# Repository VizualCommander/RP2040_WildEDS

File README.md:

# RP2040_WildEDS
IoT environmental sensor used to predict wildfires

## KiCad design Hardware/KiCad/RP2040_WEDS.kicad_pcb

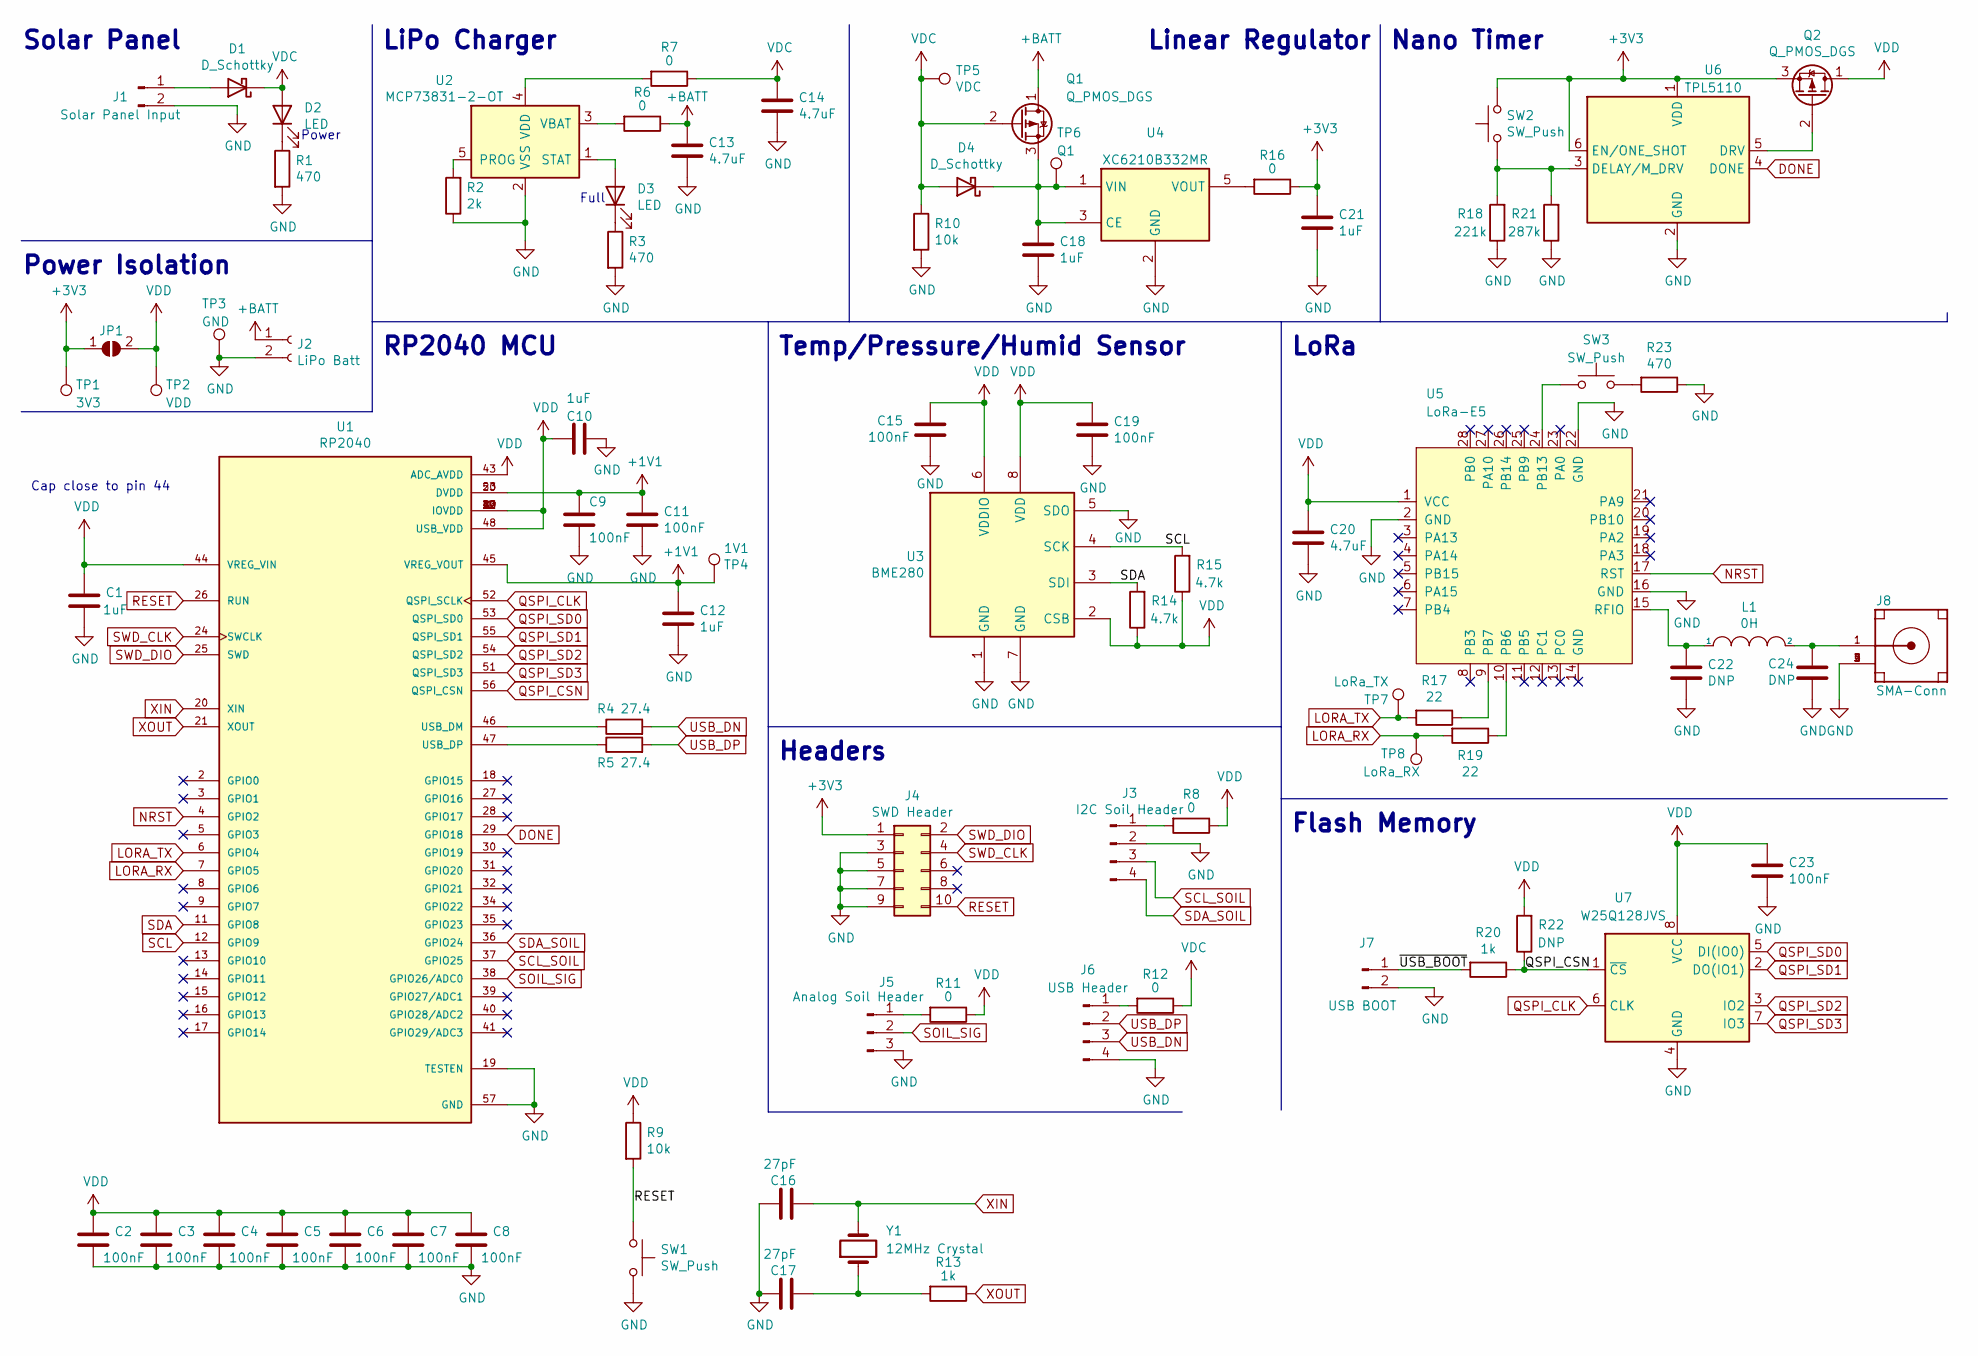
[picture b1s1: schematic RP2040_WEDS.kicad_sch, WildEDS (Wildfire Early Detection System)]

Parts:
C1, C10, C12, C18, C21: 1uF; C_0603_1608Metric
C2, C3, C4, C5, C6, C7, C8, C9, C11, C15, C19, C23: 100nF; C_0603_1608Metric
C13, C14, C20: 4.7uF; C_0603_1608Metric
C16, C17: 27pF; C_0603_1608Metric
C22, C24: DNP; C_0603_1608Metric
D1, D4: D_Schottky; D_SOD-323
D2, D3: LED; LED_0603_1608Metric
J1: Solar Panel Input; PinHeader_1x02_P2.54mm_Horizontal
J2: LiPo Batt; PinHeader_2x01_P2.54mm_Vertical
J3: I2C Soil Header; PinHeader_1x04_P2.54mm_Horizontal
J4: SWD Header; PinHeader_2x05_P1.27mm_Vertical
J5: Analog Soil Header; PinHeader_1x03_P2.54mm_Horizontal
J6: USB Header; PinHeader_1x04_P2.54mm_Vertical
J7: USB BOOT; PinSocket_1x02_P2.54mm_Vertical
J8: SMA-Conn; SMA_Amphenol_132289_EdgeMount_new; PARTREV K
JP1: Power Isolation; SolderJumper-2_P1.3mm_Open_RoundedPad1.0x1.5mm
L1: 0H; L_0603_1608Metric
Q1, Q2: Q_PMOS_DGS; SOT-23
R1, R3, R23: 470; R_0603_1608Metric
R2: 2k; R_0603_1608Metric
R4, R5: 27.4; R_0603_1608Metric
R6, R7, R8, R11, R12, R16: 0; R_0603_1608Metric
R9, R10: 10k; R_0603_1608Metric
R13, R20: 1k; R_0603_1608Metric
R14, R15: 4.7k; R_0603_1608Metric
R17, R19: 22; R_0603_1608Metric
R18: 221k; R_0603_1608Metric
R21: 287k; R_0603_1608Metric
R22: DNP; R_0603_1608Metric
SW1, SW2, SW3: SW_Push; SW_Push_1P1T_NO_6x6mm_H9.5mm
TP1: 3V3; TestPoint_Loop_D1.80mm_Drill1.0mm_Beaded
TP2: VDD; TestPoint_Loop_D1.80mm_Drill1.0mm_Beaded
TP3: GND; TestPoint_Loop_D1.80mm_Drill1.0mm_Beaded
TP4: 1V1; TestPoint_Loop_D1.80mm_Drill1.0mm_Beaded
TP5: VDC; TestPoint_Loop_D1.80mm_Drill1.0mm_Beaded
TP6: Q1; TestPoint_Loop_D1.80mm_Drill1.0mm_Beaded
TP7: LoRa_TX; TestPoint_Loop_D1.80mm_Drill1.0mm_Beaded
TP8: LoRa_RX; TestPoint_Loop_D1.80mm_Drill1.0mm_Beaded
U1: RP2040; QFN40P700X700X90-57N; PARTREV 1.6.1
U2: MCP73831-2-OT; SOT-23-5
U3: BME280; Bosch_LGA-8_2.5x2.5mm_P0.65mm_ClockwisePinNumbering
U4: XC6210B332MR; SOT-23-5
U5: LoRa-E5
U6: TPL5110; SOT-23-6
U7: W25Q128JVS; SOIC-8_5.23x5.23mm_P1.27mm
Y1: 12MHz Crystal; XTAL1140X470X420N

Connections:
+1V1: C9.1, C11.1, C12.1, TP4.1, U1.23 (DVDD), U1.45 (VREG_VOUT), U1.50 (DVDD)
+3V3: C21.1, J4.1, JP1.1 (A), Q2.3 (S), R16.1, SW2.2, TP1.1, U6.1 (VDD), U6.6 (EN/ONE_SHOT)
+BATT: C13.1, J2.1, Q1.1 (D), R6.1
/~USB_BOOT: J7.1, R20.2
DONE: U1.29 (GPIO18), U6.4 (DONE)
GND: C1.2, C2.2, C3.2, C4.2, C5.2, C6.2, C7.2, C8.2, C9.2, C10.1, C11.2, C12.2, C13.2, C14.2, C15.2, C16.1, C17.1, C18.2, C19.2, C20.2, C21.2, C22.2, C23.2, C24.2, J1.2, J2.2, J3.2, J4.3, J4.5, J4.7, J4.9, J5.3, J6.4, J7.2, J8.2, J8.3, J8.4, J8.5, R1.2, R2.1, R3.2, R10.2, R18.1, R21.1, R23.1, SW1.2, TP3.1, U1.19 (TESTEN), U1.57 (GND), U2.2 (VSS), U3.1 (GND), U3.5 (SDO), U3.7 (GND), U4.2 (GND), U5.2 (GND), U5.16 (GND), U5.22 (GND), U6.2 (GND), U7.4 (GND)
LORA_RX: R19.2, TP8.1, U1.7 (GPIO5)
LORA_TX: R17.2, TP7.1, U1.6 (GPIO4)
NRST: U1.4 (GPIO2), U5.17 (RST)
unnamed: C17.2, R13.2, Y1.1
unnamed: C18.1, D4.1 (K), Q1.3 (S), TP6.1, U4.1 (VIN), U4.3 (CE)
unnamed: C22.1, L1.1, U5.15 (RFIO)
unnamed: C24.1, J8.1, L1.2
unnamed: D1.2 (A), J1.1
unnamed: D2.1 (K), R1.1
unnamed: D3.1 (K), R3.1
unnamed: D3.2 (A), U2.1 (STAT)
unnamed: J3.1, R8.2
unnamed: J5.1, R11.2
unnamed: J6.1, R12.2
unnamed: Q2.2 (G), U6.5 (DRV)
unnamed: R2.2, U2.5 (PROG)
unnamed: R4.1, U1.46 (USB_DM)
unnamed: R5.1, U1.47 (USB_DP)
unnamed: R6.2, U2.3 (VBAT)
unnamed: R7.2, U2.4 (VDD)
unnamed: R16.2, U4.5 (VOUT)
unnamed: R17.1, U5.9 (PB7)
unnamed: R18.2, R21.2, SW2.1, U6.3 (DELAY/M_DRV)
unnamed: R19.1, U5.10 (PB6)
unnamed: R23.2, SW3.2
unnamed: SW3.1, U5.24 (PB13~)
QSPI_CLK: U1.52 (QSPI_SCLK), U7.6 (CLK)
QSPI_CSN: R20.1, R22.1, U1.56 (QSPI_CSN), U7.1 (~CS)
QSPI_SD0: U1.53 (QSPI_SD0), U7.5 (DI(IO0))
QSPI_SD1: U1.55 (QSPI_SD1), U7.2 (DO(IO1))
QSPI_SD2: U1.54 (QSPI_SD2), U7.3 (IO2)
QSPI_SD3: U1.51 (QSPI_SD3), U7.7 (IO3)
RESET: J4.10, R9.2, SW1.1, U1.26 (RUN)
SCL: R15.2, U1.12 (GPIO9), U3.4 (SCK)
SCL_SOIL: J3.3, U1.37 (GPIO25)
SDA: R14.2, U1.11 (GPIO8), U3.3 (SDI)
SDA_SOIL: J3.4, U1.36 (GPIO24)
SOIL_SIG: J5.2, U1.38 (GPIO26/ADC0)
SWD_CLK: J4.4, U1.24 (SWCLK)
SWD_DIO: J4.2, U1.25 (SWD)
USB_DN: J6.3, R4.2
USB_DP: J6.2, R5.2
VDC: C14.1, D1.1 (K), D2.2 (A), D4.2 (A), Q1.2 (G), R7.1, R10.1, R12.1, TP5.1
VDD: C1.1, C2.1, C3.1, C4.1, C5.1, C6.1, C7.1, C8.1, C10.2, C15.1, C19.1, C20.1, C23.1, JP1.2 (B), Q2.1 (D), R8.1, R9.1, R11.1, R14.1, R15.1, R22.2, TP2.1, U1.1 (IOVDD), U1.10 (IOVDD), U1.22 (IOVDD), U1.33 (IOVDD), U1.42 (IOVDD), U1.43 (ADC_AVDD), U1.44 (VREG_VIN), U1.48 (USB_VDD), U1.49 (IOVDD), U3.2 (CSB), U3.6 (VDDIO), U3.8 (VDD), U5.1 (VCC), U7.8 (VCC)
XIN: C16.2, U1.20 (XIN), Y1.2
XOUT: R13.1, U1.21 (XOUT)

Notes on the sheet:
LiPo Charger
Linear Regulator
Solar Panel
RP2040 MCU
Full
Headers
Power Isolation
Nano Timer
LoRa
Temp/Pressure/Humid Sensor
Power
Flash Memory
Cap close to pin 44

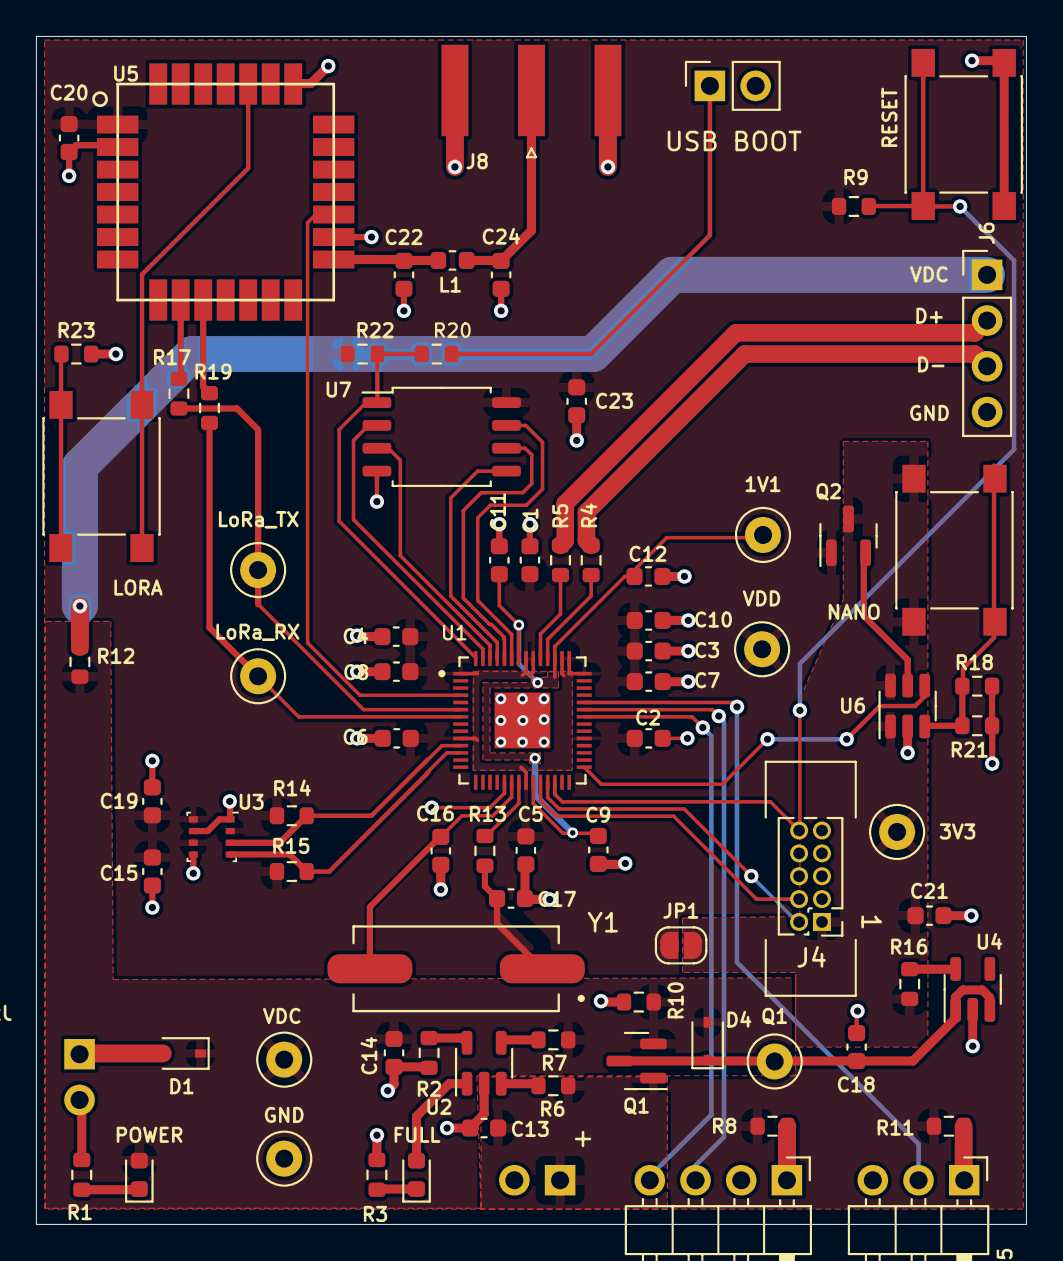
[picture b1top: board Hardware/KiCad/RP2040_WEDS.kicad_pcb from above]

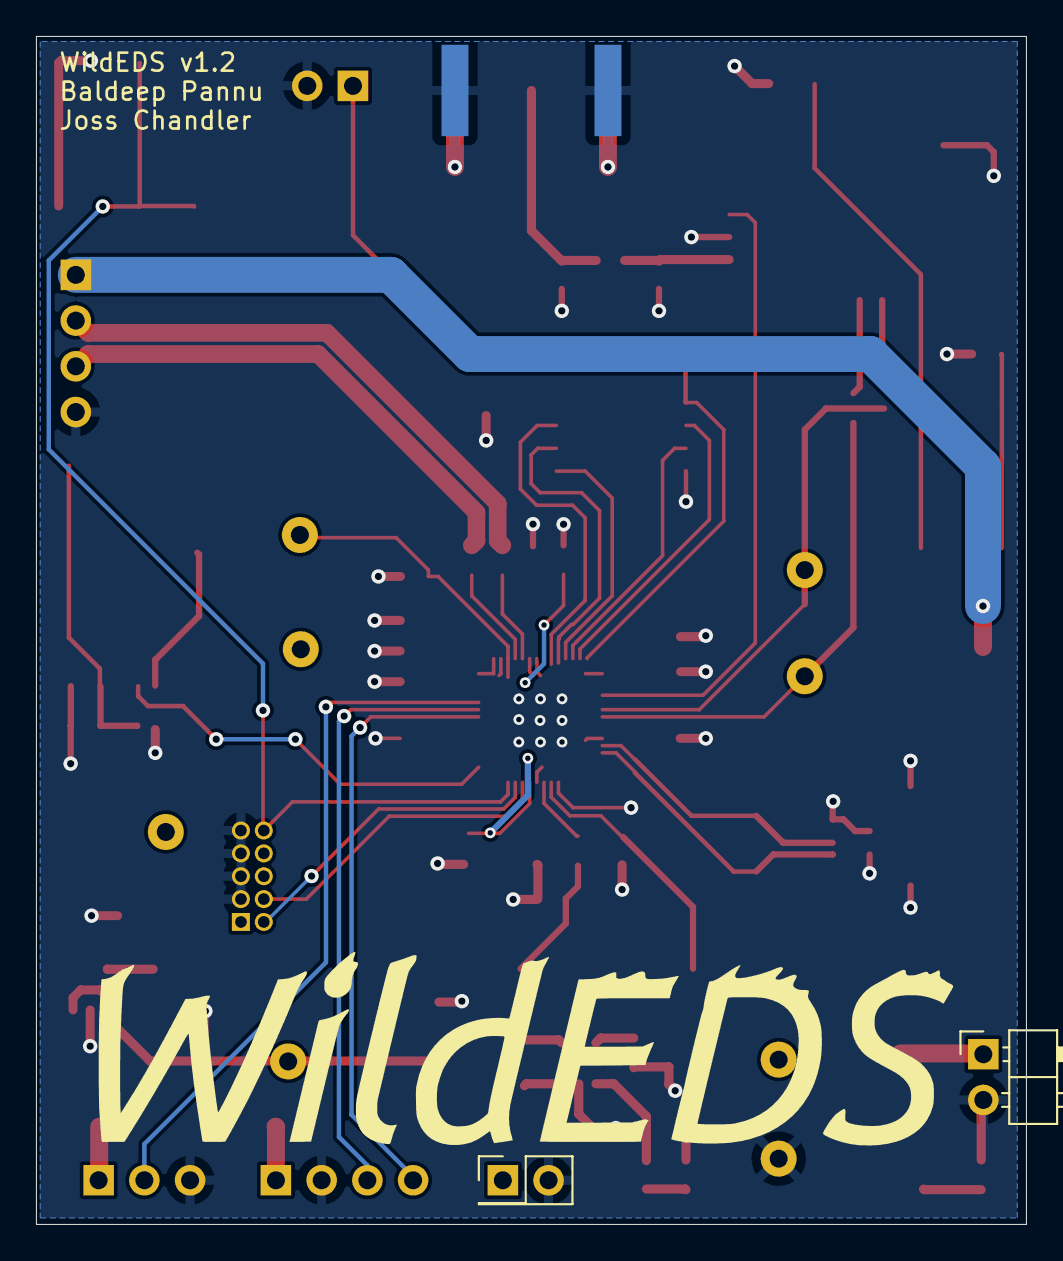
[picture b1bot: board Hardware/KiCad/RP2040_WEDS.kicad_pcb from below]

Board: 2 copper layers, 55.0 x 66.0 mm, 82 parts (2 on the bottom side), 52 nets.

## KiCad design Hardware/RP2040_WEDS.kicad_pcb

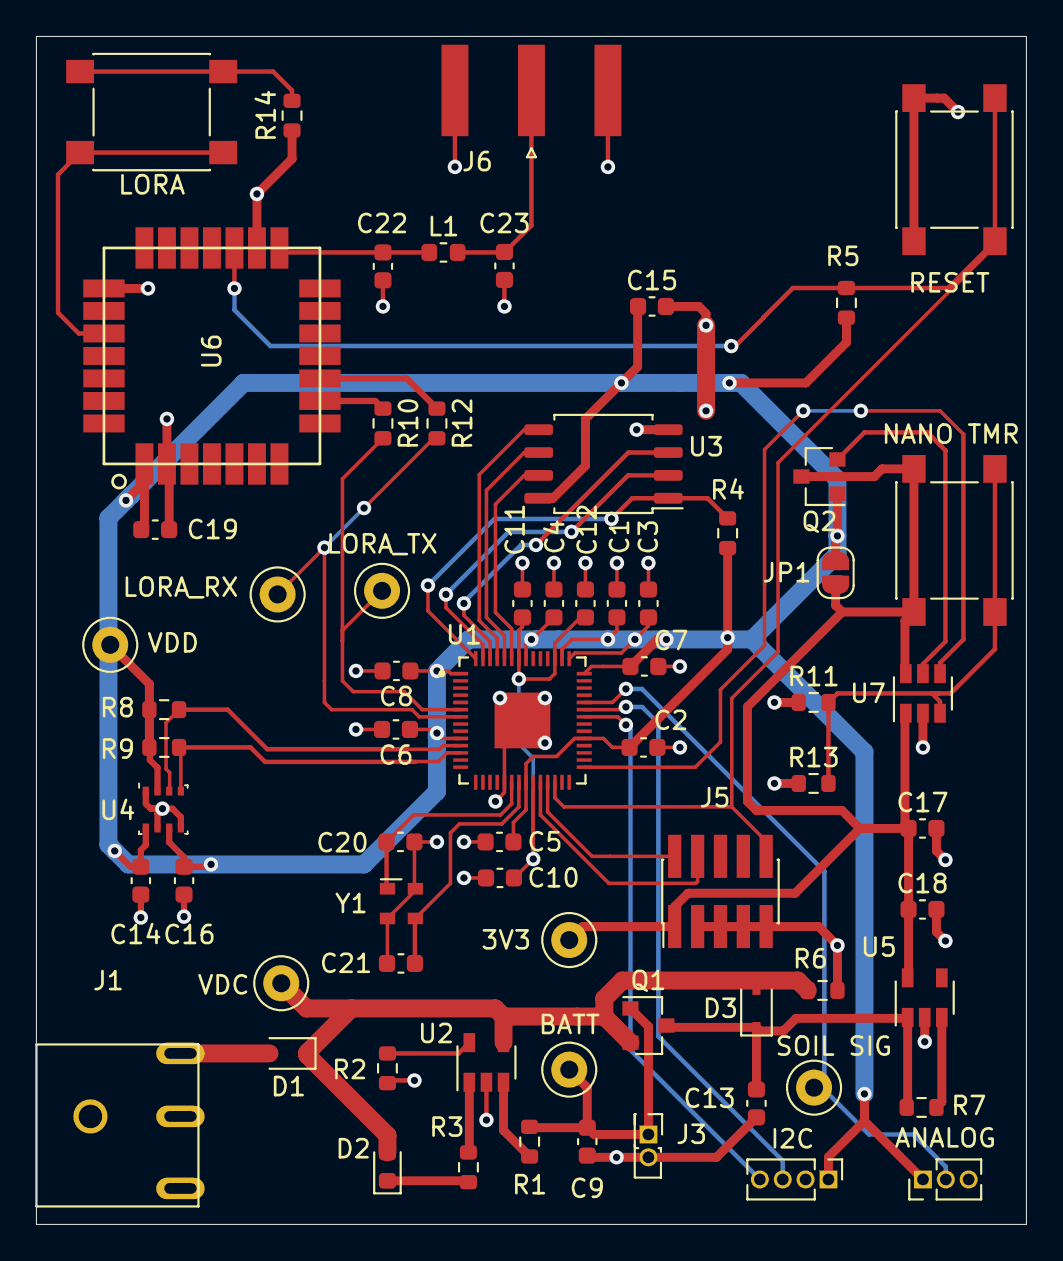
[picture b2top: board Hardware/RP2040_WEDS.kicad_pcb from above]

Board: 2 copper layers, 55.0 x 66.0 mm, 68 parts (0 on the bottom side), 40 nets.

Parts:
3V3: TestPoint; TestPoint_Loop_D1.80mm_Drill1.0mm_Beaded
ANALOG: Conn_01x03_Male; PinHeader_1x03_P1.27mm_Vertical
BATT: TestPoint; TestPoint_Loop_D1.80mm_Drill1.0mm_Beaded
C1, C12: 1uF; C_0603_1608Metric
C2, C3, C4, C5, C6, C7, C8, C10, C11, C14, C16: 100nF; C_0603_1608Metric
C9, C13, C17, C18: 10uF; C_0603_1608Metric
C15: C; C_0603_1608Metric
C19: 4.7uF; C_0603_1608Metric
C20, C21: 8pF; C_0603_1608Metric
C22, C23: DNP; C_0603_1608Metric
D1, D3: D_Schottky; D_SOD-323
D2: LED; LED_0603_1608Metric
I2C: Conn_01x04_Male; PinHeader_1x04_P1.27mm_Vertical
J1: Barrel_Jack_Switch_Pin3Ring; 54-00125
J3: LiPo Batt; PinHeader_2x01_P1.27mm_Vertical
J5: Conn_02x05_Odd_Even; PinHeader_2x05_P1.27mm_Vertical_SMD
J6: SMA-J-P-H-RA-TH1; SMA_Amphenol_132289_EdgeMount_new
JP1: SolderJumper_2_Open; SolderJumper-2_P1.3mm_Open_RoundedPad1.0x1.5mm
L1: 0H; L_0603_1608Metric
LORA: SW_Push; SW_Push_1P1T_NO_6x6mm_H9.5mm
LORA_RX: TestPoint; TestPoint_Loop_D1.80mm_Drill1.0mm_Beaded
LORA_TX: TestPoint; TestPoint_Loop_D1.80mm_Drill1.0mm_Beaded
NANO TMR: SW_Push; SW_Push_1P1T_NO_6x6mm_H9.5mm
Q1, Q2: Q_PMOS_DGS; SOT-23
R1: 0; R_0603_1608Metric
R2: 2k; R_0603_1608Metric
R3, R4, R5, R6, R7, R8, R9: 10k; R_0603_1608Metric
R10, R12: 22; R_0603_1608Metric
R11: 221k; R_0603_1608Metric
R13: 287k; R_0603_1608Metric
R14: 470; R_0603_1608Metric
RESET: SW_Push; SW_Push_1P1T_NO_6x6mm_H9.5mm
SOIL SIG: TestPoint; TestPoint_Loop_D1.80mm_Drill1.0mm_Beaded
U1: RP2040; QFN40P700X700X90-57N
U2: MCP73831-2-OT; SOT-23-5
U3: W25Q128JVS; SOIC-8_5.23x5.23mm_P1.27mm
U4: BME280; Bosch_LGA-8_2.5x2.5mm_P0.65mm_ClockwisePinNumbering
U5: AP2112K-3.3; SOT-23-5
U6: LoRa-E5
U7: TPL5110; SOT-23-6
VDC: TestPoint; TestPoint_Loop_D1.80mm_Drill1.0mm_Beaded
VDD: TestPoint; TestPoint_Loop_D1.80mm_Drill1.0mm_Beaded
Y1: Crystal_GND24; Oscillator_SMD_Abracon_ASDMB-4Pin_2.5x2.0mm

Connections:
+1V1: C10.1, C11.1, C12.1, U1.23, U1.45, U1.50
+3V3: 3V3.1, C17.1, C18.1, J5.1, JP1.1, NANO TMR.2, Q2.3, U5.5, U7.1, U7.6
+BATT: BATT.1, C9.1, J3.1, Q1.1, R1.1
DONE: U1.29, U7.4
GND: ANALOG.3, C1.2, C2.2, C3.2, C4.2, C5.2, C6.2, C7.2, C8.2, C9.2, C10.2, C11.2, C12.2, C13.2, C14.2, C15.2, C16.2, C17.2, C18.2, C19.2, C20.2, C21.1, C22.2, C23.2, I2C.2, J1.2, J1.3, J3.2, J5.3, J5.5, J5.7, J5.9, J6.2, J6.3, J6.4, J6.5, R2.1, R6.2, R11.1, R13.1, R14.1, RESET.2, U1.19, U1.57, U2.2, U3.4, U4.1, U4.5, U4.7, U5.2, U6.2, U6.16, U6.22, U7.2, Y1.2, Y1.4
LORA_RX: LORA_RX.1, R12.2, U1.7
LORA_TX: LORA_TX.1, R10.2, U1.6
unnamed: C13.1, D3.1, Q1.3, R7.2, U5.1
unnamed: C22.1, L1.1, U6.15
unnamed: C23.1, J6.1, L1.2
unnamed: D1.2, J1.1
unnamed: D2.1, R3.1
unnamed: Q2.2, U7.5
unnamed: R1.2, U2.3
unnamed: R2.2, U2.5
unnamed: R3.2, U2.1
unnamed: R7.1, U5.3
unnamed: R10.1, U6.9
unnamed: NANO TMR.1, R11.2, R13.2, U7.3
unnamed: R12.1, U6.10
unnamed: LORA.2, R14.2
unnamed: LORA.1, U6.24
QSPI_CLK: U1.52, U3.6
QSPI_CSN: R4.1, U1.56, U3.1
QSPI_SD0: U1.53, U3.5
QSPI_SD1: U1.55, U3.2
QSPI_SD2: U1.54, U3.3
QSPI_SD3: U1.51, U3.7
RESET: J5.10, R5.2, RESET.1, U1.26, U6.17
SCL: R9.2, U1.12, U4.4
SCL_SOIL: I2C.3, U1.37
SDA: R8.2, U1.11, U4.3
SDA_SOIL: I2C.4, U1.36
SOIL_SIG: ANALOG.2, SOIL SIG.1, U1.38
SWD_CLK: J5.4, U1.24
SWD_DIO: J5.2, U1.25
VDC: D1.1, D2.2, D3.2, Q1.2, R6.1, U2.4, VDC.1
VDD: ANALOG.1, C1.1, C2.1, C3.1, C4.1, C5.1, C6.1, C7.1, C8.1, C14.1, C15.1, C16.1, C19.1, I2C.1, JP1.2, Q2.1, R4.2, R5.1, R8.1, R9.1, U1.1, U1.10, U1.22, U1.33, U1.42, U1.43, U1.44, U1.49, U3.8, U4.2, U4.6, U4.8, U6.1, VDD.1
XIN: C20.1, U1.20, Y1.1
XOUT: C21.2, U1.21, Y1.3

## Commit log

2022-02-11 KiCad files added
2022-02-11 Test push
2022-02-11 updated gerber files
2022-02-11 added KiCad folder
2022-02-11 added altium folder
2022-02-11 added new folders and Altium files
2022-02-11 added proposal docs
2022-02-11 altium libraries added
2022-02-11 created kicad gerber subfolder
2022-02-11 Imported kicad to altium
2022-02-15 changed solder bridge position between 3V3 and VDD
2022-02-15 Rearranged components around lipo charger
2022-02-17 Added power fills for 3V3, VDD and VDC
2022-02-17 PCB changes
2022-02-17 nothing
2022-02-21 Removed files
2022-02-21 Updated filepaths
2022-02-21 Deleted unnecessary files
2022-02-21 Adjusted copper fill
2022-02-21 Added thermal relief
2022-02-22 Changed Batt to go on bottom layer
2022-02-23 Updated power plane
2022-02-23 interactive BOM
2022-02-23 added thermal relief to fill zones
2022-02-23 checked off sourced parts in BOM
2022-03-01 stencil added
2022-03-02 changed the size of headers form 1.27 to 2.54mm
2022-03-02 updated schematic
2022-03-03 fixed component values
2022-03-07 Version 1.2 board
2022-03-08 v1.2
2022-03-09 added lables and boxes to schematic
2022-03-15 added documents
2022-03-29 fixed traces
